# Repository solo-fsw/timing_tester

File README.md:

# Timing Tester

**Protocol commands**
| Event | Command (decimal)	| Note |
| ------------- | ------------- | ------------- | 
| MYINFO |	80	|  |
| PING	| 81	|  |
| RESETTESTER	| 90	|  |
| TESTINGFINISHED	| 91	|  |
| DISPLAYTESTSETUP| 100	|  |
| AUDIOTESTSETUP	| 101 |  |
| SRBOXTESTSETUP	| 102	|  |
| MARKER|109	|  |
| STARTDISPLAYTEST	|110	|  |
| STARTAUDIOTEST	| 111	|  |
| STARTSRBOXTEST | 112	|  |
| STOPTESTER	| 115	|  |
| DUMPDISPLAYDATA	| 48	|  |
| DUMPAUDIODATA	| 151	|  |
| DUMPSRBOXDATA	| 152	|  |

# Timing Tester standalone 
<br/>

**Description**<br/>
The timingtester standalone is a easy to use tool for validating the monitor timing of your stimulus.
It's a drop in replacement for the [Usbparmarker](https://researchwiki.solo.universiteitleiden.nl/xwiki/wiki/researchwiki.solo.universiteitleiden.nl/view/Hardware/Markers%20and%20Events/UsbParMarker/) so no need to change your experiment. Future release it will also be possible to dropin replace the Eva.

**How to use**<br/>
If you have used the [Eprime](https://github.com/solo-fsw/eprime_package_markers), [OpenSesame](https://github.com/solo-fsw/opensesame_plugin_markers) or [Python](https://github.com/solo-fsw/python-markers) package for the Usbparmaker it's as simple to unplug the Usbparmarker and plugin the timingtester.
Hold the tester in the middle of the screen and start your script. On the display of the timingtester the test result will be displayed.
On the display you will see at the left upper corner the last measurement. V is for video, A for audio but this is not implement yet.
In the upper right corner is the last marker value is shown.

For correct timing is important that you change your slide from dark to light to activate the lightsensor. After timing testing you can always set the screen color back to the desired color.

If you are not using one of our packages for the Usbparmarker you have to look up yourself the comport in the windows devicemanager and change this in your script.

**What is a correct response time**<br/>
That's hard to say and depends on the stimules software used , hardware and your script.
Minimum response time is depending on you refresh rate. For example a 60Hz monitor has a frame duratione of 1 sec / 60Hz = 16ms. Measuring half way the screen wil give an ideal reponse of 8ms.
As seen in the example below the rest of the system eats up 3ms and the total response time wil be 11ms.
This test is done in E-prime setting the marker in the onset.
If you are in doubt, please contact labsupport the help you testing or give you advise to get the timing better.

**Advanced use**<br/>
The timingtester standalone can be placed in command mode by (re)opening the com port at 2400Baud.
The following commands are supported.
| Event | Command | Note |
| ------------- | ------------- | ------------- | 
| MYINFO |	V	|  |
| PING	| P	|  |
| RESETTESTER	| R	|  |

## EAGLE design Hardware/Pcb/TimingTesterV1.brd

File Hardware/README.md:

# Hardware
This folder will contain the Timing Tester's firmware and PCB source files.

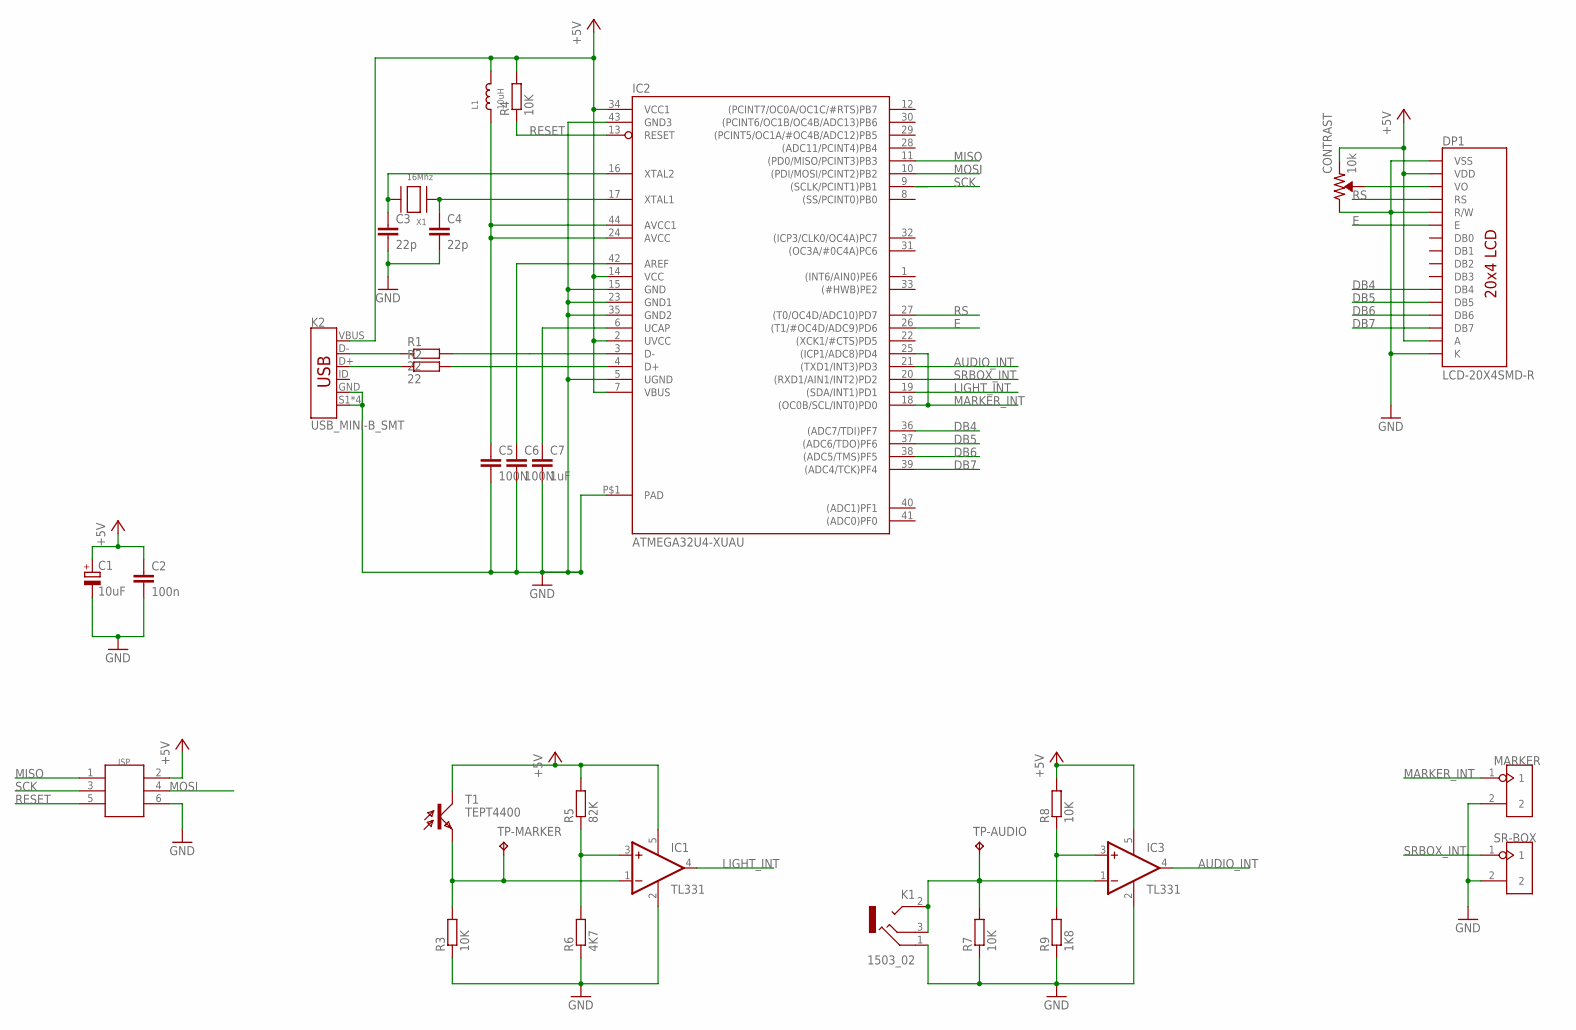
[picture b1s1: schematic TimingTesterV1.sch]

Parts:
C1: 10uF; R/2012-12R
C2: 100n; C0805
C3, C4: 22p; C0805; FARNELL 1759489
C5, C6: 100N; C0805
C7: 1uF; C0805
CONTRAST: 10k; TRIMPOT-SMD-TC33X; FARNELL 1689863
DP1: LCD-20X4SMD-R; LCD-20X4-SMD
IC1, IC3: TL331; DBV-R-PDSO-G5; FARNELL 1470409
IC2: ATMEGA32U4-XUAU; TQFP44-PAD
ISP: HEADER-2X3P-SMD; 2X3P-2.54-SMD; FARNELL 9689567
K1: 1503_02
K2: USB_MINI-B_SMT; USB-MINIB; FARNELL 1753806
L1: 10uH; 0805; FARNELL 2215650
MARKER: HEADER-2PSMD; 2P-2.54-SMD
R1, R2: 22; M0805
R3, R7, R8: 10K; R0603
R4: 10K; M0805
R5: 82K; R0603
R6: 4K7; R0603
R9: 1K8; R0603
SR-BOX: HEADER-2PSMD; 2P-2.54-SMD
T1: TEPT4400; BPX81-SMD
TP-AUDIO: TPTP20R; TP20R
TP-MARKER: TPTP20R; TP20R
X1: 16Mhz; NX5032; FARNELL 2467791

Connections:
+5V: C1.+, C2.2, CONTRAST.3 (CCW), DP1.2 (VDD), DP1.15 (A), IC1.5 (V+), IC2.2 (UVCC), IC2.7 (VBUS), IC2.14 (VCC), IC2.34 (VCC1), IC3.5 (V+), ISP.2, K2.VBUS, L1.2, R4.2, R5.2, R8.2, T1.C
AUDIO_INT: IC2.21 ((TXD1/INT3)PD3), IC3.4 (OUT)
DB4: DP1.11 (DB4), IC2.36 ((ADC7/TDI)PF7)
DB5: DP1.12 (DB5), IC2.37 ((ADC6/TDO)PF6)
DB6: DP1.13 (DB6), IC2.38 ((ADC5/TMS)PF5)
DB7: DP1.14 (DB7), IC2.39 ((ADC4/TCK)PF4)
E: DP1.6 (E), IC2.26 ((T1/#OC4D/ADC9)PD6)
GND: C1.-, C2.1, C3.2, C4.2, C5.2, C6.2, C7.2, CONTRAST.1 (CW), DP1.1 (VSS), DP1.5 (R/W), DP1.16 (K), IC1.2 (GND), IC2.5 (UGND), IC2.15 (GND), IC2.23 (GND1), IC2.35 (GND2), IC2.43 (GND3), IC2.P$1 (PAD), IC3.2 (GND), ISP.6, K1.1, K2.GND, K2.S1 (SHIELD), K2.S2 (SHIELD), K2.S3 (SHIELD), K2.S4 (SHIELD), MARKER.2, R3.1, R6.1, R7.1, R9.1, SR-BOX.2
LIGHT_INT: IC1.4 (OUT), IC2.19 ((SDA/INT1)PD1)
MARKER_INT: IC2.18 ((OC0B/SCL/INT0)PD0), IC2.25 ((ICP1/ADC8)PD4), MARKER.1
MISO: IC2.11 ((PD0/MISO/PCINT3)PB3), ISP.1
MOSI: IC2.10 ((PDI/MOSI/PCINT2)PB2), ISP.4
unnamed: K2.D-, R1.1
unnamed: K2.D+, R2.1
unnamed: IC3.1 (-IN), K1.2, K1.3, R7.2, TP-AUDIO.TP
unnamed: C5.1, IC2.24 (AVCC), IC2.44 (AVCC1), L1.1
unnamed: IC3.3 (+IN), R8.1, R9.2
unnamed: CONTRAST.2 (WIPER), DP1.3 (VO)
unnamed: IC1.1 (-IN), R3.2, T1.E, TP-MARKER.TP
unnamed: IC1.3 (+IN), R5.1, R6.2
unnamed: IC2.3 (D-), R1.2
unnamed: IC2.4 (D+), R2.2
unnamed: C6.1, IC2.42 (AREF)
unnamed: C3.1, IC2.16 (XTAL2), X1.P$2
unnamed: C7.1, IC2.6 (UCAP)
unnamed: C4.1, IC2.17 (XTAL1), X1.P$1
RESET: IC2.13 (RESET), ISP.5, R4.1
RS: DP1.4 (RS), IC2.27 ((T0/OC4D/ADC10)PD7)
SCK: IC2.9 ((SCLK/PCINT1)PB1), ISP.3
SRBOX_INT: IC2.20 ((RXD1/AIN1/INT2)PD2), SR-BOX.1

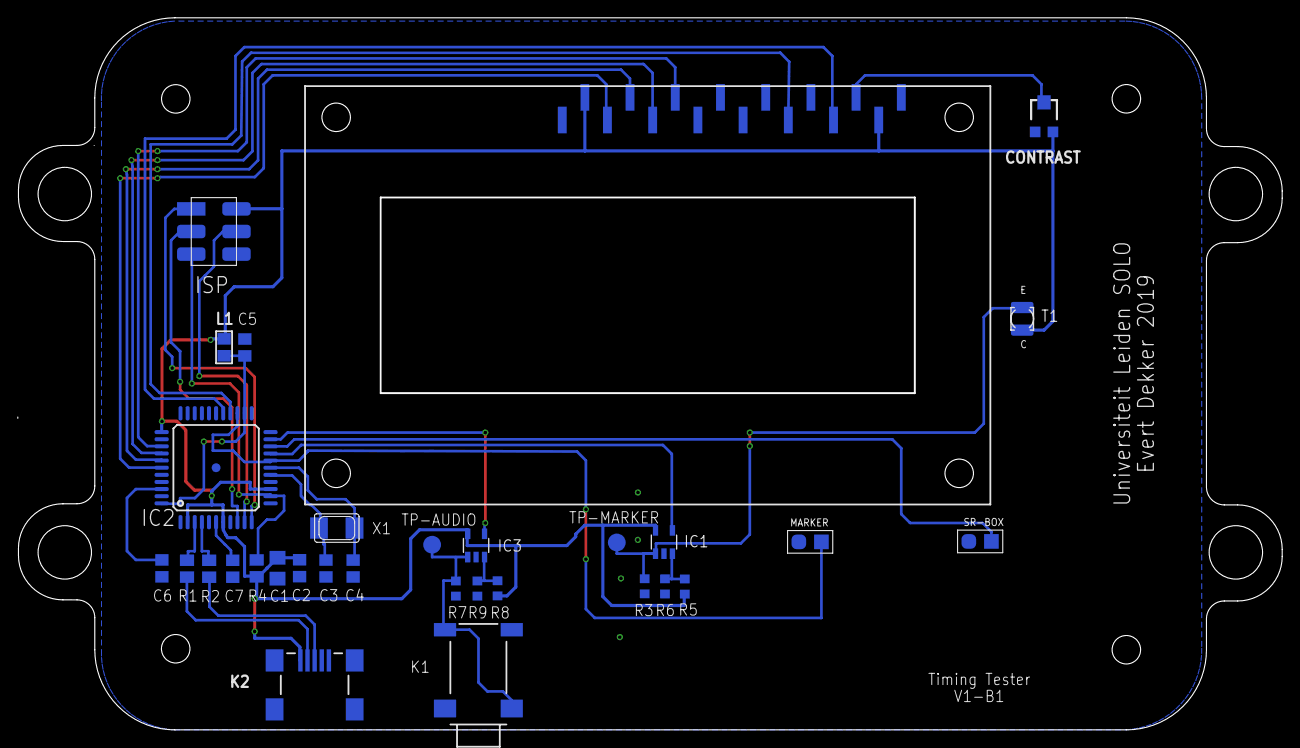
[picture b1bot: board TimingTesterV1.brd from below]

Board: 2 copper layers, 142.0 x 80.0 mm, 31 parts (30 on the bottom side), 30 nets.

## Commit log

2022-06-14 InitialPush
    Eprime TestScript for the timingtester
2022-06-14 InitialFirmwarePush
2022-06-14 Initial
2023-03-17 Eprime es3
2024-10-07 Added Standalone version
2024-10-09 InitialRelease
    First working release
2024-10-21 Added S no
2024-10-25 Update README.md
    Added standalone timing tester
2024-10-25 Added sample task
2025-12-15 Changed device name
2026-02-20 Added schematic pdf

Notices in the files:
parts and their libraries:
SparkFun-Connectors: Licensing: Creative Commons ShareAlike 4.0 International - https://creativecommons.org/licenses/by-sa/4.0
microbuilder: This work is placed in the public domain, and may be freely used for commercial and non-commercial work with the following conditions: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
